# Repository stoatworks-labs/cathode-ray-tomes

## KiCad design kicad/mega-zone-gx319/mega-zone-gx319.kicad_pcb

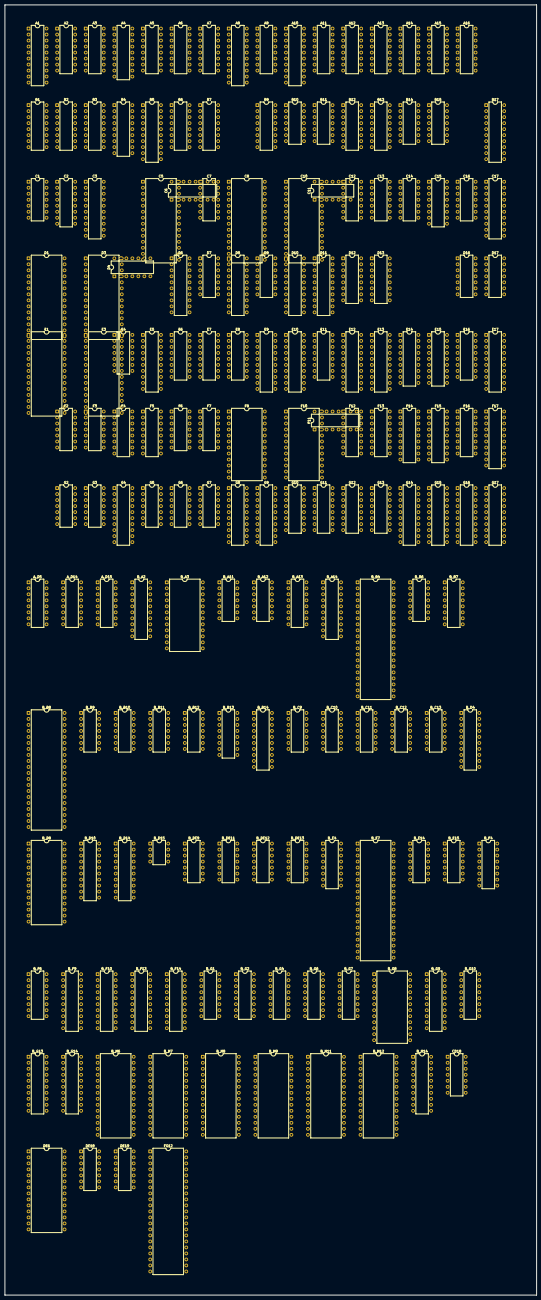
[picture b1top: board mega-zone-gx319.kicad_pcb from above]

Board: 2 copper layers, 224.9 x 545.8 mm, 171 parts (0 on the bottom side), 762 nets, no tracks yet.

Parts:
A1: 74LS244; DIP-20_W7.62mm
A2, A3: 74LS161; DIP-16_W7.62mm
A4: SRAM1K4B; DIP-18_W7.62mm
A5, A7, A9, A13, A14: 74LS157; DIP-16_W7.62mm
A6: 74LS375; DIP-16_W7.62mm
A8, A10: 74LS377; DIP-20_W7.62mm
A11: PROM256W4B; DIP-16_W7.62mm
A12, A15: 74LS174; DIP-16_W7.62mm
A16: PROM32W8B; DIP-16_W7.62mm
A_D5: 74LS157; DIP-16_W7.62mm
A_D14, A_D15: 74LS161; DIP-16_W7.62mm
B1, B6: 74LS157; DIP-16_W7.62mm
B2, B3, B12, B13: 74LS161; DIP-16_W7.62mm
B4: SRAM1K4B; DIP-18_W7.62mm
B5, B17: 74LS244; DIP-20_W7.62mm
B7: 74LS375; DIP-16_W7.62mm
B9: 74LS174; DIP-16_W7.62mm
B10, B15: 74LS86; DIP-14_W7.62mm
B11: 74LS32; DIP-14_W7.62mm
B14: 74LS04; DIP-14_W7.62mm
B_A2: 74LS373; DIP-20_W7.62mm
B_A3: 27C32; DIP-24_W15.24mm
B_A11: 74LS04; DIP-14_W7.62mm
B_A12: 74LS293; DIP-14_W7.62mm
B_A13: 74LS259; DIP-16_W7.62mm
B_A14: 74LS244; DIP-20_W7.62mm
B_B4: 8039; DIP-40_W15.24mm
B_B6: M5224P; DIP-14_W7.62mm
B_B7: 74LS138; DIP-16_W7.62mm
B_B8: AY-3-8910; DIP-40_W15.24mm
B_B9, B_B10, B_B11: 74LS293; DIP-14_W7.62mm
B_B12: 74LS32; DIP-14_W7.62mm
B_B13: 74LS139; DIP-16_W7.62mm
B_B14: 74LS240; DIP-20_W7.62mm
B_C9, B_C10, B_C12: 74LS74; DIP-14_W7.62mm
B_C11, B_C13: 74LS08; DIP-14_W7.62mm
B_D4: 74LS374; DIP-20_W7.62mm
B_D8: 501; DIP-28_W15.24mm
B_D10: 74LS244; DIP-20_W7.62mm
B_D14: 74LS240; DIP-20_W7.62mm
B_D15: 555; DIP-8_W7.62mm
B_DE9, B_DE12: 74LS32; DIP-14_W7.62mm
B_DE11: 74LS02; DIP-14_W7.62mm
B_DE13: 74LS00; DIP-14_W7.62mm
B_E4: 74LS253; DIP-16_W7.62mm
B_E7: Z80; DIP-40_W15.24mm
B_E14, B_E15: 74LS293; DIP-14_W7.62mm
B_F4: 74LS253; DIP-16_W7.62mm
B_F6: 74LS157; DIP-16_W7.62mm
B_F9, B_F10: 74LS245; DIP-20_W7.62mm
B_F13: 74LS244; DIP-20_W7.62mm
B_F14: 74LS240; DIP-20_W7.62mm
B_G1, B_G2: 74LS257; DIP-16_W7.62mm
B_G4: 74LS253; DIP-16_W7.62mm
B_G6, B_G7: 74LS157; DIP-16_W7.62mm
B_G8: SRAM2K8B; DIP-24_W15.24mm
B_G9: 74LS373; DIP-20_W7.62mm
B_G10: 74LS138; DIP-16_W7.62mm
B_G13: 74LS244; DIP-20_W7.62mm
B_G14: 74LS240; DIP-20_W7.62mm
B_H6, B_H7, B_H8, B_H9, B_H11, B_H12: 27C64; DIP-28_W15.24mm
B_H14: 74LS245; DIP-20_W7.62mm
C1: 74LS08; DIP-14_W7.62mm
C2: 74LS157; DIP-16_W7.62mm
C3: 74LS273; DIP-20_W7.62mm
C5: 083; DIP-28_W15.24mm
C6: PROM256W4B; DIP-16_W7.62mm
C7: 74LS21; DIP-14_W7.62mm
C8, C10: 27C64; DIP-28_W15.24mm
C11, C14: 74LS74; DIP-14_W7.62mm
C12, C13: 74LS86; DIP-14_W7.62mm
C15: 74LS161; DIP-16_W7.62mm
C16: 74LS107; DIP-14_W7.62mm
C17: 74LS240; DIP-20_W7.62mm
CD18: 74LS00; DIP-14_W7.62mm
D1, D3: 27C64; DIP-28_W15.24mm
D4, D9: 74LS86; DIP-14_W7.62mm
D6: 74LS377; DIP-20_W7.62mm
D7, D16: 74LS20; DIP-14_W7.62mm
D8, D10, D11: 74LS273; DIP-20_W7.62mm
D12, D13: 74LS283; DIP-16_W7.62mm
D17: 74LS32; DIP-14_W7.62mm
DE6: 27C64; DIP-28_W15.24mm
DE18: 74LS08; DIP-14_W7.62mm
DE19: 74LS10; DIP-14_W7.62mm
E1, E3: 27C64; DIP-28_W15.24mm
E4: 74LS86; DIP-14_W7.62mm
E5: 74LS273; DIP-20_W7.62mm
E6, E11: 74LS174; DIP-16_W7.62mm
E7, E8: PROM32W8B; DIP-16_W7.62mm
E9: 74LS377; DIP-20_W7.62mm
E10, E17: 74LS240; DIP-20_W7.62mm
E12: 74LS244; DIP-20_W7.62mm
E13: 74LS374; DIP-20_W7.62mm
E14, E15: SRAM1K4B; DIP-18_W7.62mm
E16: 74LS157; DIP-16_W7.62mm
F2: 74LS164; DIP-14_W7.62mm
F3: 74LS08; DIP-14_W7.62mm
F4: 74LS161; DIP-16_W7.62mm
F5: 74LS138; DIP-16_W7.62mm
F6: 74LS74; DIP-14_W7.62mm
F7: 74LS10; DIP-14_W7.62mm
F8, F10: SRAM2K8B; DIP-24_W15.24mm
F11, F16: 74LS157; DIP-16_W7.62mm
F12, F13: 74LS283; DIP-16_W7.62mm
F14, F15: SRAM1K4B; DIP-18_W7.62mm
F17: 74LS240; DIP-20_W7.62mm
FG12: KONAMI-1; DIP-42_W15.24mm
G2: 74LS164; DIP-14_W7.62mm
G3, G5: 74LS32; DIP-14_W7.62mm
G4: 74LS240; DIP-20_W7.62mm
G6, G7: 74LS74; DIP-14_W7.62mm
G8, G9, G16, G17: 74LS245; DIP-20_W7.62mm
G10, G11: 74LS157; DIP-16_W7.62mm
G12, G13: 74LS283; DIP-16_W7.62mm
G14, G15: 74LS374; DIP-20_W7.62mm

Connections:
/Color mixer/CFIX: B11.9, C11.8
/Color mixer/OCOL0: A7.4, A14.2
/Color mixer/OCOL1: A7.7, A14.5
/Color mixer/OCOL2: A7.9, A14.11
/Color mixer/OCOL3: A7.12, A14.14
/Color mixer/SEL: B1.4, B11.10
/Color mixer/TCOL''0: A13.4, A14.3
/Color mixer/TCOL''1: A13.7, A14.6
/Color mixer/TCOL''2: A13.9, A14.10
/Color mixer/TCOL''3: A13.12, A14.13
/Color mixer/~BLANK: C17.17, DE19.10, G6.9
/Color mixer/~CHBLANK: B9.7, B17.11, DE19.11
/IO/DB0: B_B8.37, B_D4.3, B_D8.20, B_E4.7, B_E7.14, B_G2.4, DE6.11
/IO/DB1: B_B8.36, B_D4.4, B_D8.21, B_E4.9, B_E7.15, B_G2.7, DE6.12
/IO/DB2: B_B8.35, B_D4.7, B_D8.22, B_E7.12, B_F4.7, B_G2.9, DE6.13
/IO/DB3: B_B8.34, B_D4.8, B_D8.23, B_E7.8, B_F4.9, B_G2.12, DE6.15
/IO/DB4: B_B8.33, B_D4.13, B_D8.24, B_E7.7, B_G1.4, B_G4.7, DE6.16
/IO/DB5: B_B8.32, B_D4.14, B_D8.25, B_E7.9, B_G1.7, B_G4.9, DE6.17
/IO/DB6: B_B8.31, B_D4.17, B_D8.26, B_E7.10, B_G1.9, DE6.18
/IO/DB7: B_B8.30, B_D4.18, B_D8.27, B_E7.13, B_G1.12, DE6.19
/IO/~AFR1: B_B13.11, B_DE13.9
/IO/~AFR2: B_B12.8, B_DE13.13
/IO/~CABINP: B_B7.12, B_E4.1, B_E4.15, B_F4.1, B_F4.15, B_G4.1, B_G4.15
/IO/~CSYNC: B17.8, C17.8, DE18.11
/IO/~DIP: B_B7.11, B_G1.15, B_G2.15
/IO/~VBLANK: B_B14.3, B_D14.2, B_E14.10, B_E15.10
/Main CPU/BLANK: B_C9.11, B_C12.3, B_D14.18
/Main CPU/CLKE: B_D10.14, FG12.15
/Main CPU/CLKQ: B_D10.16, FG12.17
/Main CPU/H1B: B_A14.5, B_C10.11, B_D8.10, B_D14.6, B_D14.15
/Main CPU/H2B: B_A14.7, B_C10.12, B_D8.9, B_D10.6, B_D14.4, B_DE9.12, B_F6.1, B_G6.1, B_G7.1
/Main CPU/INTSND: B_A14.16, B_C9.3
/Main CPU/INTST: B_A14.14, B_C12.4
/Main CPU/LACH: B_D14.13, B_D14.14, B_G9.11
/Main CPU/MA0: B_F14.13, B_G13.9, B_H6.10, B_H7.10, B_H8.10, B_H9.10, B_H11.10, B_H12.10
/Main CPU/MA1: B_A13.1, B_F14.11, B_G13.12, B_H6.9, B_H7.9, B_H8.9, B_H9.9, B_H11.9, B_H12.9
/Main CPU/MA2: B_A13.2, B_F14.8, B_G13.7, B_H6.8, B_H7.8, B_H8.8, B_H9.8, B_H11.8, B_H12.8
/Main CPU/MA3: B_A13.3, B_G13.14, B_G14.17, B_H6.7, B_H7.7, B_H8.7, B_H9.7, B_H11.7, B_H12.7
/Main CPU/MA4: B_G13.5, B_G14.2, B_H6.6, B_H7.6, B_H8.6, B_H9.6, B_H11.6, B_H12.6
/Main CPU/MA5: B_G13.16, B_G14.15, B_H6.5, B_H7.5, B_H8.5, B_H9.5, B_H11.5, B_H12.5
/Main CPU/MA6: B_G13.3, B_G14.4, B_H6.4, B_H7.4, B_H8.4, B_H9.4, B_H11.4, B_H12.4
/Main CPU/MA7: B_G13.18, B_G14.13, B_H6.3, B_H7.3, B_H8.3, B_H9.3, B_H11.3, B_H12.3
/Main CPU/MA8: B_F13.9, B_G14.6, B_H6.25, B_H7.25, B_H8.25, B_H9.25, B_H11.25, B_H12.25
/Main CPU/MA9: B_F13.12, B_G14.11, B_H6.24, B_H7.24, B_H8.24, B_H9.24, B_H11.24, B_H12.24
/Main CPU/MA10: B_F13.7, B_G14.8, B_H6.21, B_H7.21, B_H8.21, B_H9.21, B_H11.21, B_H12.21
/Main CPU/MA11: B_B13.2, B_B13.14, B_F13.14, B_H6.23, B_H7.23, B_H8.23, B_H9.23, B_H11.23, B_H12.23
/Main CPU/MA12: B_B13.3, B_B13.13, B_F13.5, B_H6.2, B_H7.2, B_H8.2, B_H9.2, B_H11.2, B_H12.2
/Main CPU/MA13: B_F13.18, B_G10.1
/Main CPU/MA14: B_DE11.6, B_F13.3, B_G10.2
/Main CPU/MA15: B_DE11.5, B_F13.16, B_G10.3
/Main CPU/MA'0: B_G6.10, F16.13, F17.18, G10.13
/Main CPU/MA'1: B_G6.6, F16.6, F17.14, G10.10
/Main CPU/MA'2: B_G6.13, F16.10, F17.7, G10.6
/Main CPU/MA'3: B_G6.3, F16.3, F17.5, G11.3
/Main CPU/MA'4: B_F6.10, E16.10, E17.16, G10.3
/Main CPU/MA'5: B_F6.6, E16.13, E17.18, G11.13
/Main CPU/MA'6: B_F6.13, E16.3, E17.3, F11.6
/Main CPU/MA'7: B_F6.3, E16.6, E17.14, F11.3
/Main CPU/MA'8: B_G7.3, DE18.9, F11.13, F17.16
/Main CPU/MA'9: B_G7.6, DE18.4, F11.10, F17.3
/Main CPU/MA'10: B_G7.13, F17.12, G11.10
/Main CPU/MA''0: B_G13.11, FG12.30
/Main CPU/MA''1: B_G13.8, FG12.31
/Main CPU/MA''2: B_G13.13, FG12.32
/Main CPU/MA''3: B_G13.6, FG12.33
/Main CPU/MA''4: B_G13.15, FG12.34
/Main CPU/MA''5: B_G13.4, FG12.35
/Main CPU/MA''6: B_G13.17, FG12.36
/Main CPU/MA''7: B_G13.2, FG12.37
/Main CPU/MA''8: B_F13.11, FG12.38
/Main CPU/MA''9: B_F13.8, FG12.39
/Main CPU/MA''10: B_F13.13, FG12.40
/Main CPU/MA''11: B_F13.6, FG12.41
/Main CPU/MA''12: B_F13.15, FG12.42
/Main CPU/MA''13: B_F13.2, FG12.1
/Main CPU/MA''14: B_F13.17, FG12.2
/Main CPU/MA''15: B_F13.4, FG12.3
/Main CPU/MBS: B_F14.2, FG12.26
/Main CPU/MD0: B_F9.11, G8.11, G9.11, G14.13, G15.13, G16.11, G17.9
/Main CPU/MD1: B_F9.12, G8.12, G9.12, G14.8, G15.8, G16.12, G17.8
/Main CPU/MD2: B_F9.13, G8.13, G9.13, G14.14, G15.14, G16.13, G17.7
/Main CPU/MD3: B_F9.14, G8.14, G9.14, G14.7, G15.7, G16.14, G17.6
/Main CPU/MD4: B_F9.15, G8.15, G9.15, G14.17, G15.17, G16.15, G17.5
/Main CPU/MD5: B_F9.16, G8.16, G9.16, G14.4, G15.4, G16.16, G17.4
/Main CPU/MD6: B_F9.17, G8.17, G9.17, G14.18, G15.18, G16.17, G17.3
/Main CPU/MD7: B_F9.18, G8.18, G9.18, G14.3, G15.3, G16.18, G17.2
/Main CPU/MD'0: B_A13.13, B_F10.9, B_G9.2, B_G9.3, B_H6.11, B_H7.11, B_H8.11, B_H9.11, B_H11.11, B_H12.11, B_H14.16
/Main CPU/MD'1: B_F10.8, B_G9.4, B_G9.5, B_H6.12, B_H7.12, B_H8.12, B_H9.12, B_H11.12, B_H12.12, B_H14.14
/Main CPU/MD'2: B_F10.7, B_G9.6, B_G9.7, B_H6.13, B_H7.13, B_H8.13, B_H9.13, B_H11.13, B_H12.13, B_H14.12
/Main CPU/MD'3: B_F10.6, B_G9.8, B_G9.9, B_H6.15, B_H7.15, B_H8.15, B_H9.15, B_H11.15, B_H12.15, B_H14.11
/Main CPU/MD'4: B_F10.5, B_G9.12, B_G9.13, B_H6.16, B_H7.16, B_H8.16, B_H9.16, B_H11.16, B_H12.16, B_H14.13
/Main CPU/MD'5: B_F10.4, B_G9.14, B_G9.15, B_H6.17, B_H7.17, B_H8.17, B_H9.17, B_H11.17, B_H12.17, B_H14.15
/Main CPU/MD'6: B_F10.3, B_G9.16, B_G9.17, B_H6.18, B_H7.18, B_H8.18, B_H9.18, B_H11.18, B_H12.18, B_H14.17
/Main CPU/MD'7: B_F10.2, B_G9.18, B_G9.19, B_H6.19, B_H7.19, B_H8.19, B_H9.19, B_H11.19, B_H12.19, B_H14.18
/Main CPU/MD''0: B_H14.4, G17.11
/Main CPU/MD''1: B_H14.6, G17.12
/Main CPU/MD''2: B_H14.8, G17.13
/Main CPU/MD''3: B_H14.9, G17.14
/Main CPU/MD''4: B_H14.7, G17.15
/Main CPU/MD''5: B_H14.5, G17.16
/Main CPU/MD''6: B_H14.3, G17.17
/Main CPU/MD''7: B_H14.2, G17.18
/Main CPU/MD'''0: B_F10.11, FG12.12
/Main CPU/MD'''1: B_F10.12, FG12.10
/Main CPU/MD'''2: B_F10.13, FG12.9
/Main CPU/MD'''3: B_F10.14, FG12.8
/Main CPU/MD'''4: B_F10.15, FG12.7
/Main CPU/MD'''5: B_F10.16, FG12.6
/Main CPU/MD'''6: B_F10.17, FG12.5
/Main CPU/MD'''7: B_F10.18, FG12.4
/Main CPU/MRD: B_B14.11, B_D10.12, B_DE12.13, B_DE13.5, B_H14.1
/Main CPU/MRD': E17.9, F17.11, G17.1
/Main CPU/MR~W: B_D10.8, B_F10.1, FG12.13
/Main CPU/MWR: D16.4, DE19.4, F17.9
/Main CPU/~CRAM': C17.14, D17.12
/Main CPU/~CRAM: B_B13.5, B_B14.4, B_C13.4
/Main CPU/~FIRQ: B_C12.9, FG12.25
/Main CPU/~INTMAIN: B_B7.10, B_C12.11
/Main CPU/~IRQ: B_C12.5, FG12.24
/Main CPU/~LACH: B_D14.7, B_DE12.12, B_DE13.4
/Main CPU/~LATCHOE: B_DE12.8, B_DE13.2, B_G9.1
/Main CPU/~MLATCH: B_A13.14, B_B13.12
/Main CPU/~MROM0: B_G10.13, B_H12.20
/Main CPU/~MROM1: B_G10.12, B_H11.20
/Main CPU/~MROM2: B_G10.11, B_H9.20
/Main CPU/~MROM3: B_G10.10, B_H8.20
/Main CPU/~MROM4: B_G10.9, B_H7.20
/Main CPU/~MROM5: B_G10.7, B_H6.20
/Main CPU/~MSHRAM: B_B13.7, B_C13.1, B_DE9.2, B_F9.19
/Main CPU/~OBJRAM: B11.12, E17.5, G16.19
/Main CPU/~RESET: B_A13.15, B_B4.4, B_B8.23, B_B14.8, B_C11.9, B_C11.12, B_C13.8, B_E7.26, FG12.19
/Main CPU/~SCROLLX: E17.12, G14.11
/Main CPU/~SCROLLY: E17.7, G15.11
/Main CPU/~VRAM': C17.16, D17.1
/Main CPU/~VRAM: B_B13.4, B_B14.2, B_C13.5
/Objects 2/COL10: A7.3, B6.2, B7.3
/Objects 2/COL11: A7.6, B6.5, B7.5
/Objects 2/COL12: A7.10, B6.11, B7.11
/Objects 2/COL13: A7.13, B6.14, B7.13
/Objects 2/COL20: A5.2, A6.3, A7.2
/Objects 2/COL21: A5.5, A6.5, A7.5
/Objects 2/COL22: A5.11, A6.11, A7.11
/Objects 2/COL23: A5.14, A6.13, A7.14
/Objects 2/COL'0: A5.3, B6.3, C6.12
/Objects 2/COL'1: A5.6, B6.6, C6.11
/Objects 2/COL'2: A5.10, B6.10, C6.10
/Objects 2/COL'3: A5.13, B6.13, C6.9
/Objects 2/OCLK1: A1.11, B2.2, B3.2, B5.19, C2.4
/Objects 2/OCLK2: A1.6, A2.2, A3.2, B5.1, C2.7
/Objects 2/OCLK3: B7.4, B7.12, C2.9
/Objects 2/OCLK4: A6.4, A6.12, C2.12
/Objects 2/OPCK: C2.2, C2.6, C2.11, C2.13, C5.1, D6.11, G4.9
/Objects 2/PXCK1: B17.4, C2.10, C2.14, C17.18
/Objects 2/PXCK2: C2.3, C2.5, E10.16
/Objects 2/XPOS10: B2.14, B4.17
/Objects 2/XPOS11: B2.13, B4.4
/Objects 2/XPOS12: B2.12, B4.5
/Objects 2/XPOS13: B2.11, B4.7
/Objects 2/XPOS14: B3.14, B4.3
/Objects 2/XPOS15: B3.13, B4.16
/Objects 2/XPOS16: B3.12, B4.15
/Objects 2/XPOS17: B3.11, B4.6
/Objects 2/XPOS20: A2.14, A4.1
/Objects 2/XPOS21: A2.13, A4.17
/Objects 2/XPOS22: A2.12, A4.16
/Objects 2/XPOS23: A2.11, A4.15
/Objects 2/XPOS24: A3.14, A4.2
/Objects 2/XPOS25: A3.13, A4.3
/Objects 2/XPOS26: A3.12, A4.4
/Objects 2/XPOS27: A3.11, A4.5
/Objects 2/~COL10: B7.2, C7.12
/Objects 2/~COL11: B7.6, C7.10
/Objects 2/~COL12: B7.10, C7.13
/Objects 2/~COL13: B7.14, C7.9
/Objects 2/~COL20: A6.2, C7.1
/Objects 2/~COL21: A6.6, C7.2
/Objects 2/~COL22: A6.10, C7.4
/Objects 2/~COL23: A6.14, C7.5
/Objects 2/~LB1EN: A5.15, B1.1, C1.12, C14.9
/Objects 2/~LB2EN: A7.1, B6.15, C1.1, C2.1, C14.8, C14.12
/Objects 2/~OBEN1: B4.8, C1.11
/Objects 2/~OBEN2: A4.8, C1.3
/Objects 2/~OBEN'': C1.2, C1.13, D6.12
/Objects 2/~ODB5L1: B1.12, B2.9, B3.9
/Objects 2/~ODB5L2: A2.9, A3.9, B1.9
/Objects 2/~OSEL1: B1.2, B6.1, C7.8
/Objects 2/~OSEL2: A5.1, B1.3, C7.6
/Objects/COL0: C5.16, C6.5
/Objects/COL1: C5.13, C6.6
/Objects/COL2: C5.17, C6.7
/Objects/COL3: C5.12, C6.4
/Objects/DMA: CD18.1, DE19.1, G7.8
/Objects/FLIPX: E5.4, E6.12
/Objects/FLIPX': D6.8, E4.10, E4.12, E5.5
/Objects/FLIPX'': C5.2, D6.9
/Objects/FLIPY: E5.7, E6.10
/Objects/FLIPY': D4.2, D4.5, D4.13, E4.5, E5.6
/Objects/H2': C17.7, D16.5, DE18.5, DE18.10, DE19.5, E13.11, E16.1, F16.1
/Objects/OA0: A_D15.14, E14.5, E15.5, F16.14
/Objects/OA1: A_D15.13, E14.6, E15.6, F16.5
/Objects/OA2: A_D15.12, E14.7, E15.7, F7.13, F16.11
/Objects/OA3: A_D15.11, E14.4, E15.4, F7.2, F16.2
/Objects/OA4: A_D14.14, E14.3, E15.3, E16.11
/Objects/OA5: A_D14.13, E14.2, E15.2, E16.14
/Objects/OA6: A_D14.12, E14.1, E15.1, E16.2
/Objects/OA7: A_D14.11, E14.17, E15.17, E16.5, F7.1
/Objects/OBA0: F14.5, F15.5, F16.12
/Objects/OBA1: F14.6, F15.6, F16.7
/Objects/OBA2: F14.7, F15.7, F16.9
/Objects/OBA3: F14.4, F15.4, F16.4
/Objects/OBA4: E16.9, F14.3, F15.3
/Objects/OBA5: E16.12, F14.2, F15.2
/Objects/OBA6: E16.4, F14.1, F15.1
/Objects/OBA7: E16.7, F14.17, F15.17
/Objects/OBA8: DE18.8, F14.16, F15.16
/Objects/OBA9: DE18.6, F14.15, F15.15
/Objects/OBD0: E13.4, F15.14, G16.5
/Objects/OBD1: E13.17, F15.13, G16.4
/Objects/OBD2: E13.7, F15.12, G16.3
/Objects/OBD3: E13.13, F15.11, G16.2
/Objects/OBD4: E13.18, F14.14, G16.9
/Objects/OBD5: E13.3, F14.13, G16.8
/Objects/OBD6: E13.14, F14.12, G16.7
/Objects/OBD7: E13.8, F14.11, G16.6
/Objects/OCA0: D4.4, E5.15
/Objects/OCA1: D4.12, E5.19
/Objects/OCA2: D4.1, E5.2
/Objects/OCA3: E4.4, E5.16
/Objects/OCD0: C5.6, E1.11, E3.11
/Objects/OCD1: C5.10, E1.12, E3.12
/Objects/OCD2: C5.23, E1.13, E3.13
/Objects/OCD3: C5.19, E1.15, E3.15
/Objects/OCD4: C5.5, E1.16, E3.16
/Objects/OCD5: C5.9, E1.17, E3.17
/Objects/OCD6: C5.24, E1.18, E3.18
/Objects/OCD7: C5.20, E1.19, E3.19
/Objects/OCD8: C5.4, D1.11, D3.11
/Objects/OCD9: C5.8, D1.12, D3.12
/Objects/OCD10: C5.25, D1.13, D3.13
/Objects/OCD11: C5.21, D1.15, D3.15
/Objects/OCD12: C5.3, D1.16, D3.16
/Objects/OCD13: C5.7, D1.17, D3.17
/Objects/OCD14: C5.26, D1.18, D3.18
/Objects/OCD15: C5.22, D1.19, D3.19
/Objects/OCHA0: D1.10, D3.10, D4.6, E1.10, E3.10
/Objects/OCHA1: D1.9, D3.9, D4.11, E1.9, E3.9
/Objects/OCHA2: D1.8, D3.8, D4.3, E1.8, E3.8
/Objects/OCHA3: D1.7, D3.7, E1.7, E3.7, E4.11
/Objects/OCHA4: D1.6, D3.6, E1.6, E3.6, E4.8
/Objects/OCHA5: D1.5, D3.5, E1.5, E3.5, E4.6
/Objects/OCHA6: C3.9, D1.4, D3.4, E1.4, E3.4
/Objects/OCHA7: C3.6, D1.3, D3.3, E1.3, E3.3
/Objects/OCHA8: C3.5, D1.25, D3.25, E1.25, E3.25
/Objects/OCHA9: C3.2, D1.24, D3.24, E1.24, E3.24
/Objects/OCHA10: C3.15, D1.21, D3.21, E1.21, E3.21
/Objects/OCHA11: C3.16, D1.23, D3.23, E1.23, E3.23
/Objects/OCHA12: C3.19, D1.2, D3.2, E1.2, E3.2
/Objects/OD0: E12.4, E13.5, E14.14
/Objects/OD1: E12.15, E13.16, E14.13
/Objects/OD2: E12.6, E13.6, E14.12
/Objects/OD3: E12.8, E13.12, E14.11
/Objects/OD4: E12.17, E13.19, E15.14
/Objects/OD5: E12.2, E13.2, E15.13
/Objects/OD6: E12.13, E13.15, E15.12
/Objects/OD7: E12.11, E13.9, E15.11
/Objects/OD'0: A2.3, B2.3, C3.8, D11.14, E6.4, E12.16
/Objects/OD'1: A2.4, B2.4, C3.7, D11.18, E6.3, E12.5
/Objects/OD'2: A2.5, B2.5, C3.4, D11.3, E6.6, E12.14
/Objects/OD'3: A2.6, B2.6, C3.3, D11.4, E6.14, E12.12
/Objects/OD'4: A3.3, B3.3, C3.14, D11.7, E12.3
/Objects/OD'5: A3.4, B3.4, C3.17, D11.13, E12.18
/Objects/OD'6: A3.5, B3.5, C3.18, D11.8, E6.13, E12.7
/Objects/OD'7: A3.6, B3.6, C3.13, D11.17, E6.11, E12.9
/Objects/OP0OP1: C5.27, F3.3
/Objects/PAL0: D6.3, E6.5
/Objects/PAL1: D6.4, E6.2
/Objects/PAL2: D6.7, E6.7
/Objects/PAL3: D6.18, E6.15
/Objects/PAL'0: C6.3, D6.2
/Objects/PAL'1: C6.2, D6.5
/Objects/PAL'2: C6.1, D6.6
/Objects/PAL'3: C6.15, D6.19
/Objects/V1: B12.7, B12.10, C12.1, C14.5, D12.5
/Objects/V2: B12.14, C12.4, D12.3
/Objects/V4: B12.13, C12.9, D12.14
/Objects/V8: B12.12, C12.12, D12.12
/Objects/V16: B12.11, C13.1, D13.5, G6.11
/Objects/V32: B13.14, C13.4, D13.3, F7.5
/Objects/V64: B13.13, C13.9, D13.14, F7.4
/Objects/V128: B13.12, C13.12, D13.12, F7.3
/Objects/WRIH: D16.2, DE19.2, DE19.3, E10.5
/Objects/YPOS0: D11.15, D12.6
/Objects/YPOS1: D11.19, D12.2
/Objects/YPOS2: D11.2, D12.15
/Objects/YPOS3: D11.5, D12.11
/Objects/YPOS4: D11.6, D13.6
/Objects/YPOS5: D11.12, D13.2
/Objects/YPOS6: D11.9, D13.15
/Objects/YPOS7: D11.16, D13.11
/Objects/~DMWR: DE19.12, E14.10, E15.10
/Objects/~OACNTEN': F6.9, G5.10
/Objects/~OBEN': D6.13, G5.8
/Objects/~OBEN: E5.12, G5.9
/Objects/~OCHAH: D1.20, D4.8, E1.20
/Objects/~OCHAL: C3.12, D3.20, D4.9, E3.20
/Objects/~ODB0: D7.1, E6.9, F5.15
/Objects/~ODB1: D7.5, D11.11, F5.14
/Objects/~ODB3: C3.11, D7.2, E5.11, F5.12
/Objects/~ODB5: B1.11, B1.13, D6.1, F5.10, F6.11
/Objects/~OP2: E4.13, G4.5
/SA0: B_A11.9, B_B12.4, B_D10.18, B_DE11.11, B_E4.14, B_F4.14, B_G1.1, B_G2.1, B_G4.14, B_G6.11, DE6.10
/SA1: B_D10.9, B_DE11.2, B_E4.2, B_F4.2, B_G4.2, B_G6.5, DE6.9
/SA2: B_E7.32, B_G6.14, DE6.8
/SA3: B_E7.33, B_G6.2, DE6.7
/SA4: B_E7.34, B_F6.11, DE6.6
/SA5: B_E7.35, B_F6.5, DE6.5
/SA6: B_E7.36, B_F6.14, DE6.4
/SA7: B_E7.37, B_F6.2, DE6.3
/SA8: B_E7.38, B_G7.2, DE6.25
/SA9: B_E7.39, B_G7.5, DE6.24
/SA10: B_E7.40, B_G7.14, DE6.21
/Shared RAM/VA0: B_G6.9, B_G8.8
/Shared RAM/VA1: B_G6.7, B_G8.7
/Shared RAM/VA2: B_G6.12, B_G8.6
/Shared RAM/VA3: B_G6.4, B_G8.5
/Shared RAM/VA4: B_F6.9, B_G8.4
/Shared RAM/VA5: B_F6.7, B_G8.3
/Shared RAM/VA6: B_F6.12, B_G8.2
/Shared RAM/VA7: B_F6.4, B_G8.1
/Shared RAM/VA8: B_G7.4, B_G8.23
/Shared RAM/VA9: B_G7.7, B_G8.22
/Shared RAM/VA10: B_G7.12, B_G8.19
/Shared RAM/VD0: B_D8.1, B_F9.9, B_G8.9
/Shared RAM/VD1: B_D8.2, B_F9.8, B_G8.10
/Shared RAM/VD2: B_D8.3, B_F9.7, B_G8.11
/Shared RAM/VD3: B_D8.4, B_F9.6, B_G8.13
/Shared RAM/VD4: B_D8.5, B_F9.5, B_G8.14
/Shared RAM/VD5: B_D8.6, B_F9.4, B_G8.15
/Shared RAM/VD6: B_D8.7, B_F9.3, B_G8.16
/Shared RAM/VD7: B_D8.8, B_F9.2, B_G8.17
/Shared RAM/~MWRAMW: B_DE9.3, B_F9.1, B_G7.10
/Shared RAM/~SRD: B_D8.13, B_E7.21
/Shared RAM/~SSHRAM: B_B7.7, B_D8.12
/Shared RAM/~SVRAMW: B_DE9.6, B_G7.11
/Shared RAM/~WAIT: B_D8.19, B_E7.24
/Shared RAM/~WRIT: B_DE9.1, B_DE12.11
/Sub CPU/CK1M79: B_A11.12, B_B8.22
/Sub CPU/CK7M16: B_A12.9, B_A12.11, B_D14.8
/Sub CPU/IA0: B_A2.12, B_A3.8
/Sub CPU/IA1: B_A2.9, B_A3.7
/Sub CPU/IA2: B_A2.15, B_A3.6
/Sub CPU/IA3: B_A2.6, B_A3.5
/Sub CPU/IA4: B_A2.16, B_A3.4
/Sub CPU/IA5: B_A2.5, B_A3.3
/Sub CPU/IA6: B_A2.19, B_A3.2
/Sub CPU/IA7: B_A2.2, B_A3.1
/Sub CPU/IA8: B_A3.23, B_B4.21
/Sub CPU/IA9: B_A3.22, B_B4.22
/Sub CPU/IA10: B_A3.19, B_B4.23
/Sub CPU/IA11: B_A3.21, B_B4.24
/Sub CPU/ID0: B_A2.13, B_A3.9, B_B4.12, B_D4.2
/Sub CPU/ID1: B_A2.8, B_A3.10, B_B4.13, B_D4.5
/Sub CPU/ID2: B_A2.14, B_A3.11, B_B4.14, B_D4.6
/Sub CPU/ID3: B_A2.7, B_A3.13, B_B4.15, B_D4.9
/Sub CPU/ID4: B_A2.17, B_A3.14, B_B4.16, B_D4.12
/Sub CPU/ID5: B_A2.4, B_A3.15, B_B4.17, B_D4.15
/Sub CPU/ID6: B_A2.18, B_A3.16, B_B4.18, B_D4.16
/Sub CPU/ID7: B_A2.3, B_A3.17, B_B4.19, B_D4.19
/Sub CPU/SA11: B_E7.1, DE6.23
/Sub CPU/SA12: B_E7.2, DE6.2
/Sub CPU/SA13: B_B7.1, B_E7.3
/Sub CPU/SA14: B_B7.2, B_E7.4
/Sub CPU/SA15: B_B7.3, B_E7.5
/Sub CPU/YA0: B_B4.35, B_B8.21
/Sub CPU/YA1: B_B4.36, B_B8.20
/Sub CPU/YA2: B_B4.37, B_B8.19
/Sub CPU/YA4: B_B8.17, B_B9.9, B_B9.11
/Sub CPU/YA5: B_B8.16, B_B9.5
/Sub CPU/YA6: B_B8.15, B_B9.4
/Sub CPU/YA7: B_B8.14, B_B9.8
/Sub CPU/~AYBC1: B_B8.29, B_DE11.1
/Sub CPU/~AYDIR: B_B8.27, B_DE11.13
/Sub CPU/~CODE: B_B7.13, B_D4.11
/Sub CPU/~IINT: B_B4.6, B_C10.6
/Sub CPU/~IRD: B_B4.8, B_D4.1
/Sub CPU/~SINT: B_C9.8, B_E7.16
/Sub CPU/~SIORQ: B_DE9.10, B_DE12.2, B_E7.20
/Sub CPU/~SM1: B_A11.11, B_DE9.9, B_E7.27
/Sub CPU/~SMREQ: B_B7.4, B_B7.5, B_E7.19
/Sub CPU/~SNMI: B_C9.5, B_E7.17
/Sub CPU/~SRFSH: B_B7.6, B_E7.28
/Sub CPU/~SROM: B_B7.15, DE6.20
/Sub CPU/~START: B_B7.14, B_C10.3
/Sub CPU/~WDOG: B_B7.9, B_B12.5, B_B12.10
/Tiles/CD0: B9.4, F10.9, G9.9
/Tiles/CD1: B9.3, F10.10, G9.8
/Tiles/CD2: B9.13, F10.11, G9.7
/Tiles/CD3: B9.11, F10.13, G9.6
/Tiles/CD4: F10.14, G9.5
/Tiles/CD5: D10.14, F10.15, G9.4
/Tiles/CD6: D10.7, F10.16, G9.3
/Tiles/CD7: D10.18, F10.17, G9.2
/Tiles/FIX: B14.4, F12.7, G11.11, G12.7, G14.1, G15.1
/Tiles/HF2: B15.8, G12.5
/Tiles/HF4: B15.11, G12.3
/Tiles/HF8: B15.3, G12.14
/Tiles/HF16: E7.14, E8.14, E9.19, G12.12
/Tiles/HF32: E7.13, E8.13, E9.2, E10.2, G13.5
/Tiles/HF64: E9.6, G13.3
/Tiles/HF128: E9.9, G13.14
/Tiles/HS2: E11.11, G12.4
/Tiles/HS2'': B10.9, D10.12
/Tiles/HS4: E11.13, G12.1
/Tiles/HS4'': D9.9, D10.9
/Tiles/HS8: G10.14, G12.13
/Tiles/HS16: G10.11, G12.10
/Tiles/HS32: G10.5, G13.4
/Tiles/HS64: G11.2, G13.1
/Tiles/HS128: G10.2, G13.13
/Tiles/HS'2: D10.13, E11.10
/Tiles/HS'4: D10.8, E11.12
/Tiles/PXCK2': A8.11, A10.11, A12.9, A15.9, E10.3
/Tiles/SCRX0: F12.6, G14.12
/Tiles/SCRX1: F12.2, G14.9
/Tiles/SCRX2: F12.15, G14.15
/Tiles/SCRX3: F12.11, G14.6
/Tiles/SCRX4: F13.6, G14.16
/Tiles/SCRX5: F13.2, G14.5
/Tiles/SCRX6: F13.15, G14.19
/Tiles/SCRX7: F13.11, G14.2
/Tiles/SCRY0: E11.14, G15.12
/Tiles/SCRY0F: A10.12, A13.1
/Tiles/SCRY1: G12.6, G15.9
/Tiles/SCRY2: G12.2, G15.15
/Tiles/SCRY3: G12.15, G15.6
/Tiles/SCRY4: G12.11, G15.16
/Tiles/SCRY5: G13.6, G15.5
/Tiles/SCRY6: G13.2, G15.19
/Tiles/SCRY7: G13.15, G15.2
/Tiles/SCRY'0: C11.2, CD18.12, E11.15
/Tiles/SCRY''0: B9.15, B10.12
/Tiles/TA0: F8.8, F10.8, G10.12
/Tiles/TA1: F8.7, F10.7, G10.9
/Tiles/TA2: F8.6, F10.6, G10.7
/Tiles/TA3: F8.5, F10.5, G11.4
/Tiles/TA4: F8.4, F10.4, G10.4
/Tiles/TA5: F8.3, F10.3, G11.12
/Tiles/TA6: F8.2, F10.2, F11.7
/Tiles/TA7: F8.1, F10.1, F11.4
/Tiles/TA8: F8.23, F10.23, F11.12
/Tiles/TA9: F8.22, F10.22, F11.9
/Tiles/TA10: F8.19, F10.19, G11.9
/Tiles/TCHA0: B10.8, C8.10, C10.10
/Tiles/TCHA1: C8.9, C10.9, D9.8
/Tiles/TCHA2: C8.8, C10.8, D9.3
/Tiles/TCHA3: C8.7, C10.7, D9.11
/Tiles/TCHA4: C8.6, C10.6, D9.6
/Tiles/TCHA5: C8.5, C10.5, D8.2
/Tiles/TCHA6: C8.4, C10.4, D8.5
/Tiles/TCHA7: C8.3, C10.3, D8.6
/Tiles/TCHA8: C8.25, C10.25, D8.19
/Tiles/TCHA9: C8.24, C10.24, D8.16
/Tiles/TCHA10: C8.21, C10.21, D8.12
/Tiles/TCHA11: C8.23, C10.23, D8.15
/Tiles/TCHA12: C8.2, C10.2, D8.9
/Tiles/TCHD0: A8.18, C8.11, C10.11
/Tiles/TCHD1: A8.17, C8.12, C10.12
/Tiles/TCHD2: A8.7, C8.13, C10.13
/Tiles/TCHD3: A8.3, C8.15, C10.15
/Tiles/TCHD4: A8.13, C8.16, C10.16
/Tiles/TCHD5: A8.14, C8.17, C10.17
/Tiles/TCHD6: A8.8, C8.18, C10.18
/Tiles/TCHD7: A8.4, C8.19, C10.19
/Tiles/TCHD'0: A8.19, A9.2
/Tiles/TCHD'1: A8.16, A9.5
/Tiles/TCHD'2: A8.6, A9.11
/Tiles/TCHD'3: A8.2, A9.14
/Tiles/TCHD'4: A8.12, A9.3
/Tiles/TCHD'5: A8.15, A9.6
/Tiles/TCHD'6: A8.9, A9.10
/Tiles/TCHD'7: A8.5, A9.13
/Tiles/TCODE0: A9.4, A11.5
/Tiles/TCODE1: A9.7, A11.6
/Tiles/TCODE2: A9.9, A11.7
/Tiles/TCODE3: A9.12, A11.4
/Tiles/TCOL0: A11.12, A12.4, A13.3
/Tiles/TCOL1: A11.11, A12.6, A13.6
/Tiles/TCOL2: A11.10, A12.11, A13.10
/Tiles/TCOL3: A11.9, A12.13, A13.13
/Tiles/TCOL'0: A12.5, A13.2
/Tiles/TCOL'1: A12.7, A13.5
/Tiles/TCOL'2: A12.10, A13.11
/Tiles/TCOL'3: A12.12, A13.14
/Tiles/THFLIP: B10.1, B10.10, D9.10, D10.6
/Tiles/TPAL0: A10.17, B9.5
/Tiles/TPAL1: A10.18, B9.2
/Tiles/TPAL2: A10.3, B9.12
/Tiles/TPAL3: A10.14, B9.10
/Tiles/TPAL'0: A10.16, A11.3
/Tiles/TPAL'1: A10.19, A11.2
/Tiles/TPAL'2: A10.2, A11.1
/Tiles/TPAL'3: A10.15, A11.15
/Tiles/TVFLIP: D9.2, D9.5, D9.13, D10.15
/Tiles/V1S': D9.1, D10.2
/Tiles/V2S': D9.12, D10.5
/Tiles/V4S': D9.4, D10.16
/Tiles/VD0: D8.3, F8.9, G8.9
/Tiles/VD1: D8.4, F8.10, G8.8
/Tiles/VD2: D8.7, F8.11, G8.7
/Tiles/VD3: D8.18, F8.13, G8.6
/Tiles/VD4: D8.17, F8.14, G8.5
/Tiles/VD5: D8.14, F8.15, G8.4
/Tiles/VD6: D8.13, F8.16, G8.3
/Tiles/VD7: D8.8, F8.17, G8.2
/Tiles/VF1: C12.3, F12.5
/Tiles/VF2: C12.6, F12.3
/Tiles/VF4: C12.8, F12.14
/Tiles/VF8: C12.11, F12.12
/Tiles/VF16: C13.3, F13.5
/Tiles/VF32: C13.6, F13.3
/Tiles/VF64: C13.8, F13.14
/Tiles/VF128: C13.11, F13.12
/Tiles/VS1: D10.3, F12.4
/Tiles/VS2: D10.4, F12.1
/Tiles/VS4: D10.17, F12.13
/Tiles/VS8: F12.10, G11.14
/Tiles/VS16: F11.5, F13.4
/Tiles/VS32: F11.2, F13.1
/Tiles/VS64: F11.14, F13.13
/Tiles/VS128: F11.11, F13.10
/Tiles/~CRAMBE: D17.10, D17.11, G9.19
/Tiles/~CRAMWR: D17.8, F10.21, G9.1
/Tiles/~FIX': C11.12, E11.5
/Tiles/~H1: D16.1, E10.6, E10.9, F11.1, G10.1, G11.1
/Tiles/~HT1: B9.9, B10.5, B11.4, D8.11, D10.11, E10.7
/Tiles/~TCHH: B14.6, C10.22
/Tiles/~TCHL: B14.5, C8.22, D10.19
/Tiles/~VRAMBE: D17.3, D17.4, G8.19
/Tiles/~VRAMWR: D17.6, F8.21, G8.1
/Timing/16H: B14.9, C15.15
/Timing/FLIP: B10.2, B10.13, B14.13, B15.2, B15.5, B15.10, B15.13, B17.5, CD18.13, D16.9, D16.10, D16.12, D16.13, E7.15
/Timing/FLIP': B15.6, C12.2, C12.5, C12.10, C12.13, C13.2, C13.5, C13.10, C13.13, F3.12, G4.4
/Timing/H1: B17.2, C11.3, C15.14, D17.2, D17.13, E10.11, E10.13, E11.9, G7.11
/Timing/H2: B15.9, B17.17, C15.13, C17.11, F3.13
/Timing/H4: B15.12, C11.11, C15.12, F3.10, G5.5
/Timing/H8: B15.1, C15.11
/Timing/HRD0: E7.1, E8.1, E9.18
/Timing/HRD1: E7.2, E8.2, E9.3
/Timing/HRD2: E7.3, E8.3, E9.4
/Timing/HRD3: E7.4, E8.4, E9.17
/Timing/HRD4: E7.5, E8.5, E9.14
/Timing/HRD5: E7.6, E8.6, E9.7
/Timing/HRD6: E7.7, E8.7, E9.8
/Timing/HRD7: E7.9, E8.9, E9.13
/Timing/HRD'2: E7.12, E8.12, E9.5
/Timing/HRD'3: E7.11, E8.11, E9.16
/Timing/HSYNC: B12.2, B13.2, C14.3, E10.12
/Timing/OACK: A_D5.3, G4.7
/Timing/OACNTEN: A_D5.13, F6.5
/Timing/OP0: F3.2, F4.14, F5.6
/Timing/OP1: F3.1, F4.13, F5.1
/Timing/OP2: F4.12, F5.2, G4.15
/Timing/OP3: E4.9, F4.11, F5.3
/Timing/PXCK2'': C15.2, C16.1, C16.6, E9.11
/Timing/V256: B13.11, DE18.12
/Timing/~16H: B14.8, E9.1
/Timing/~FIX: B14.3, E7.10, E8.10, E9.15, E11.4
/Timing/~FLIP: F3.9, G4.16
/Timing/~H2: A_D5.2, B14.11, B17.6, C17.9, C17.13
/Timing/~HBLANK: B11.2, E9.12, E11.6
/Timing/~HSYNC60: F2.13, G2.1, G2.2
/Timing/~HSYNC68: G2.10, G5.1
/Timing/~HSYNC: B11.3, DE18.13, E10.8, F2.1, F2.2
/Timing/~LBRST: A2.1, A3.1, A_D5.10, B2.1, B3.1, C14.11, F4.1, F6.4, F6.13, G5.6
/Timing/~OACNTEN: F6.6, F6.12
/Timing/~OAOF: G4.14, G7.4
/Timing/~ODB6: D7.4, F5.9
/Timing/~OPCK: F4.2, G5.11
/Timing/~PXCK2: C16.5, E10.4, E10.17
GND: A1.1, A1.10, A1.19, A4.6, A4.7, A4.9, A6.8, A7.15, A9.15, A11.8, A11.13, A11.14, A12.8, A13.15, A15.8, A16.8, A16.15, A_D5.15, B1.15, B4.1, B4.2, B4.9, B5.10, B7.8, B9.8, B10.7, B11.5, B11.7, B12.3, B12.4, B13.6, B14.7, B15.4, B15.7, B17.1, B17.10, B17.19, B_A2.1, B_A2.10, B_A3.12, B_A3.18, B_A11.7, B_A12.7, B_A12.12, B_A12.13, B_A13.8, B_A14.1, B_A14.10, B_A14.19, B_B4.1, B_B4.20, B_B6.11, B_B7.8, B_B8.1, B_B8.24, B_B9.7, B_B9.12, B_B9.13, B_B10.7, B_B10.12, B_B10.13, B_B11.7, B_B11.12, B_B11.13, B_B12.7, B_B13.8, B_B14.1, B_B14.10, B_B14.19, B_C9.7, B_C10.7, B_C11.7, B_C12.2, B_C12.7, B_C12.12, B_C13.7, B_D8.14, B_D8.15, B_D10.1, B_D10.10, B_D10.19, B_D14.1, B_D14.10, B_D14.19, B_D15.1, B_DE9.7, B_DE11.7, B_DE12.7, B_DE13.7, B_E4.8, B_E7.29, B_E14.7, B_E15.7, B_F4.8, B_F6.15, B_F10.19, B_F13.1, B_F13.10, B_F13.19, B_F14.1, B_F14.6, B_F14.10, B_F14.15, B_F14.19, B_G1.8, B_G2.8, B_G4.8, B_G6.15, B_G7.15, B_G8.12, B_G8.18, B_G8.20, B_G9.10, B_G10.4, B_G10.5, B_G10.8, B_G13.1, B_G13.10, B_G13.19, B_G14.1, B_G14.10, B_G14.19, B_H6.14, B_H6.22, B_H7.14, B_H7.22, B_H8.14, B_H8.22, B_H9.14, B_H9.22, B_H11.14, B_H11.22, B_H12.14, B_H12.22, C1.7, C2.15, C3.10, C5.14, C6.8, C6.13, C6.14, C7.7, C8.14, C8.20, C10.14, C10.20, C11.7, C12.7, C13.7, C14.7, C16.7, C17.1, C17.10, C17.19, CD18.7, D1.14, D1.22, D3.14, D3.22, D4.7, D7.7, D8.10, D9.7, D10.10, D11.10, D12.7, D16.7, D17.7, DE6.14, DE6.22, DE18.7, DE19.7, E1.14, E1.22, E3.14, E3.22, E4.7, E5.10, E6.8, E7.8, E8.8, E10.1, E10.10, E10.19, E11.8, E12.1, E12.10, E12.19, E14.8, E14.9, E14.15, E14.16, E15.8, E15.9, E15.15, E15.16, E16.15, E17.1, E17.10, E17.19, F2.7, F3.7, F5.4, F5.5, F5.8, F6.2, F6.7, F7.7, F8.12, F8.18, F8.20, F10.12, F10.18, F10.20, F11.15, F14.8, F14.9, F15.8, F15.9, F16.15, F17.1, F17.10, F17.19, FG12.20, FG12.22, G2.7, G3.7, G4.1, G4.10, G4.19, G5.7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
unnamed: A2.15, A3.7, A3.10
unnamed: A4.14, A6.15, B5.12
unnamed: A4.13, A6.9, B5.14
unnamed: A4.12, A6.7, B5.16
unnamed: A4.11, A6.1, B5.18
unnamed: A1.14, A4.10
unnamed: A5.4, B5.2
unnamed: A5.7, B5.4
unnamed: A5.9, B5.6
unnamed: A5.12, B5.8
unnamed: A9.1, B10.6
unnamed: A10.7, B10.3
unnamed: A10.13, B10.11
unnamed: A10.6, B10.4
unnamed: A8.1, A10.1, B11.6
unnamed: A14.1, A15.14, B11.8
unnamed: A14.4, A15.11
unnamed: A14.7, A15.6
unnamed: A14.9, A15.13
unnamed: A14.12, A15.4
unnamed: A14.15, DE19.8
unnamed: A15.5, A16.13
unnamed: A15.7, A16.11
unnamed: A15.10, A16.10
unnamed: A15.12, A16.12
unnamed: A15.15, A16.14
unnamed: A_D5.11, F7.8
unnamed: A_D5.1, G7.5, G7.12
unnamed: A_D14.7, A_D14.10, A_D15.15
unnamed: A_D5.4, A_D14.2, A_D15.2
unnamed: A_D14.15, G4.6
unnamed: A_D5.9, A_D14.1, A_D15.1
unnamed: A_D5.12, A_D15.7, A_D15.10
unnamed: B2.15, B3.7, B3.10
unnamed: B4.14, B5.3, B7.1
unnamed: B4.13, B5.5, B7.7
unnamed: B4.12, B5.7, B7.9
unnamed: B4.11, B5.9, B7.15
unnamed: A1.9, B4.10
unnamed: B5.11, B6.12
unnamed: B5.13, B6.9
unnamed: B5.15, B6.7
unnamed: B5.17, B6.4
unnamed: B9.6, E11.2
unnamed: B9.14, CD18.8
unnamed: B11.1, E10.18
unnamed: B11.13, DE19.6
unnamed: B12.15, B13.7, B13.10
unnamed: B12.9, B13.9, B14.2
unnamed: B13.15, B14.1
unnamed: B14.10, CD18.2, DE19.13
unnamed: C16.9, C16.12, G6.3
unnamed: B17.3, B_A14.13
unnamed: B17.9, DE19.9
unnamed: B17.13, B17.14
unnamed: B17.15, B_A14.12
unnamed: B17.16, B_A14.11
unnamed: B17.18, B_A14.15
unnamed: B_A2.11, B_B4.11
unnamed: B_A3.20, B_B4.9
unnamed: B_A11.4, B_A11.5
unnamed: B_A11.8, B_B12.9
unnamed: B_A11.10, B_DE12.1
unnamed: B_A11.6, B_A12.10
unnamed: B_A11.13, B_A12.4
unnamed: B_A12.8, B_B11.10
unnamed: B_A13.4, B_A14.17
unnamed: B_A13.5, B_A14.2
unnamed: B_A13.7, B_A14.4
unnamed: B_A13.10, B_A14.8
unnamed: B_A13.12, B_A14.6
unnamed: B_B4.5, B_B4.7
unnamed: B_B4.38, B_C10.1
unnamed: B_B4.2, B_D14.11, B_D14.12
unnamed: B_B4.3, B_D14.9
unnamed: B_B6.1, B_B6.2
unnamed: B_B10.10, B_B11.8
unnamed: B_B10.9, B_B10.11
unnamed: B_B9.10, B_B10.8
unnamed: B_B11.9, B_B11.11
unnamed: B_B12.6, B_C11.10
unnamed: B_B12.2, B_B12.13, B_D14.16
unnamed: B_B12.3, B_B13.1
unnamed: B_B13.6, B_B14.15
unnamed: B_B12.11, B_B13.15
unnamed: B_B13.10, B_B14.6
unnamed: B_B13.9, B_B14.13
unnamed: B_B14.5, E17.15
unnamed: B_B14.7, E17.8
unnamed: B_B14.9, E17.11
unnamed: B_B14.12, C17.15
unnamed: B_B14.14, E17.13
unnamed: B_B14.16, C17.6
unnamed: B_B14.17, C17.3
unnamed: B_B14.18, C17.4
unnamed: B_C9.4, B_C11.8
unnamed: B_C9.13, B_C11.11
unnamed: B_C10.8, B_D10.4, B_DE9.13
unnamed: B_C11.13, B_DE9.8
unnamed: B_C12.10, B_F14.18
unnamed: B_C13.2, B_DE11.4
unnamed: B_C13.3, B_DE13.1
unnamed: B_C13.6, B_DE12.10
unnamed: B_C13.9, B_DE11.10
unnamed: B_C13.10, B_C13.11
unnamed: B_C13.12, B_D14.3
unnamed: B_A14.9, B_D8.11
unnamed: B_D8.18, B_DE9.5
unnamed: B_D8.17, B_DE9.4
unnamed: B_D15.6, B_D15.7
unnamed: B_D14.17, B_D15.3
unnamed: B_C13.13, B_D15.2
unnamed: B_DE11.3, B_DE11.12, B_DE12.3
unnamed: B_DE12.9, B_DE13.6
unnamed: B_D10.2, B_E7.30
unnamed: B_D10.11, B_E7.31
unnamed: B_D14.5, B_E7.6
unnamed: B_E14.9, B_E14.11
unnamed: B_DE11.8, B_E14.8
unnamed: B_DE13.11, B_E14.12, B_E14.13
unnamed: B_E15.9, B_E15.11
unnamed: B_DE11.9, B_E15.8
unnamed: B_DE13.8, B_E15.12, B_E15.13
unnamed: B_F14.7, F17.2
unnamed: B_F14.9, F17.6
unnamed: B_F14.12, F17.13
unnamed: B_G7.9, B_G8.21
unnamed: B_DE9.11, B_G10.6
unnamed: B_B12.12, B_G10.15
unnamed: B_B12.1, B_G10.14
unnamed: B_G14.18, E17.4
unnamed: B_G14.9, F17.17
unnamed: B_G14.16, E17.17
unnamed: B_G14.7, E17.6
unnamed: B_G14.14, F17.4
unnamed: B_G14.5, E17.2
unnamed: B_G14.12, F17.8
unnamed: B_G14.3, F17.15
unnamed: B_DE13.3, B_H14.19
unnamed: B_DE13.10, B_DE13.12
unnamed: C11.5, CD18.4
unnamed: C14.2, C14.6
unnamed: C16.3, C16.8
unnamed: C16.2, C17.2
unnamed: G4.12, G4.13
unnamed: CD18.5, D16.8
unnamed: CD18.6, CD18.9
unnamed: CD18.10, CD18.11
unnamed: D7.6, G4.8
unnamed: D12.4, E5.14
unnamed: D12.1, E5.18
unnamed: D12.13, E5.3
unnamed: D12.10, E5.17
unnamed: D12.9, D13.7
unnamed: D7.10, D13.4
unnamed: D7.13, D13.1
unnamed: D7.12, D13.13
unnamed: D7.9, D13.10
unnamed: D16.6, D17.5, D17.9
unnamed: D7.8, E5.13
unnamed: B14.12, E8.15
unnamed: E10.14, E10.15
unnamed: E11.3, E11.7
unnamed: CD18.3, E13.1
unnamed: F2.8, G2.8, G3.8
unnamed: F3.8, G3.10
unnamed: F3.11, G3.9
unnamed: F6.3, F7.12
unnamed: F12.9, F13.7
unnamed: B11.11, F14.10, F15.10, G16.1
unnamed: G2.11, G4.2
unnamed: G4.18, G5.2
unnamed: G5.3, G5.4
unnamed: G5.13, G6.2, G6.6
unnamed: G4.11, G6.5
unnamed: F7.6, G6.12
unnamed: G6.8, G7.3
unnamed: F7.10, G7.6
unnamed: F7.9, G7.9
unnamed: G12.9, G13.7
unnamed: B17.7, G17.19
VCC: A1.20, A2.7, A2.10, A4.18, A6.16, A11.16, A12.1, A12.16, A15.1, A15.16, A16.16, A_D5.14, A_D14.9, A_D15.9, B1.10, B1.14, B2.7, B2.10, B4.18, B5.20, B7.16, B9.1, B9.16, B10.14, B11.14, B12.1, B12.5, B12.6, B13.1, B13.3, B13.4, B13.5, B14.14, B15.14, B17.20, B_A2.20, B_A3.24, B_A11.14, B_A12.14, B_A13.16, B_A14.20, B_B4.26, B_B4.40, B_B7.16, B_B8.25, B_B8.28, B_B8.40, B_B9.14, B_B10.14, B_B11.14, B_B12.14, B_B13.16, B_B14.20, B_C9.1, B_C9.2, B_C9.10, B_C9.12, B_C9.14, B_C10.2, B_C10.4, B_C10.10, B_C10.13, B_C10.14, B_C11.14, B_C12.1, B_C12.13, B_C12.14, B_C13.14, B_D8.28, B_D10.20, B_D14.20, B_D15.4, B_D15.8, B_DE9.14, B_DE11.14, B_DE12.14, B_DE13.14, B_E4.16, B_E7.11, B_E14.14, B_E15.14, B_F4.16, B_F13.20, B_F14.20, B_G1.16, B_G2.16, B_G4.16, B_G8.24, B_G9.20, B_G10.16, B_G13.20, B_G14.20, B_H6.1, B_H6.27, B_H6.28, B_H7.1, B_H7.27, B_H7.28, B_H8.1, B_H8.27, B_H8.28, B_H9.1, B_H9.27, B_H9.28, B_H11.1, B_H11.27, B_H11.28, B_H12.1, B_H12.27, B_H12.28, C1.14, C3.1, C3.20, C5.28, C6.16, C7.14, C8.1, C8.27, C8.28, C10.1, C10.27, C10.28, C11.1, C11.4, C11.10, C11.13, C11.14, C12.14, C13.14, C14.1, C14.4, C14.10, C14.13, C14.14, C15.1, C15.7, C15.9, C15.10, C16.4, C16.10, C16.11, C16.13, C16.14, C17.20, CD18.14, D1.1, D1.27, D1.28, D3.1, D3.27, D3.28, D4.10, D4.14, D7.14, D8.1, D8.20, D9.14, D10.1, D10.20, D11.1, D11.20, D16.14, D17.14, DE6.1, DE6.27, DE6.28, DE18.14, DE19.14, E1.1, E1.27, E1.28, E3.1, E3.27, E3.28, E4.14, E5.1, E5.20, E6.1, E6.16, E7.16, E8.16, E10.20, E11.1, E11.16, E12.20, E14.18, E15.18, E17.20, F2.9, F2.14, F3.14, F4.7, F4.9, F4.10, F5.16, F6.1, F6.10, F6.14, F7.11, F7.14, F8.24, F10.24, F14.18, F15.18, F17.20, FG12.29, G2.9, G2.14, G3.14, G4.20, G5.14, G6.1, G6.4, G6.10, G6.13, G6.14, G7.1, G7.10, G7.13, G7.14

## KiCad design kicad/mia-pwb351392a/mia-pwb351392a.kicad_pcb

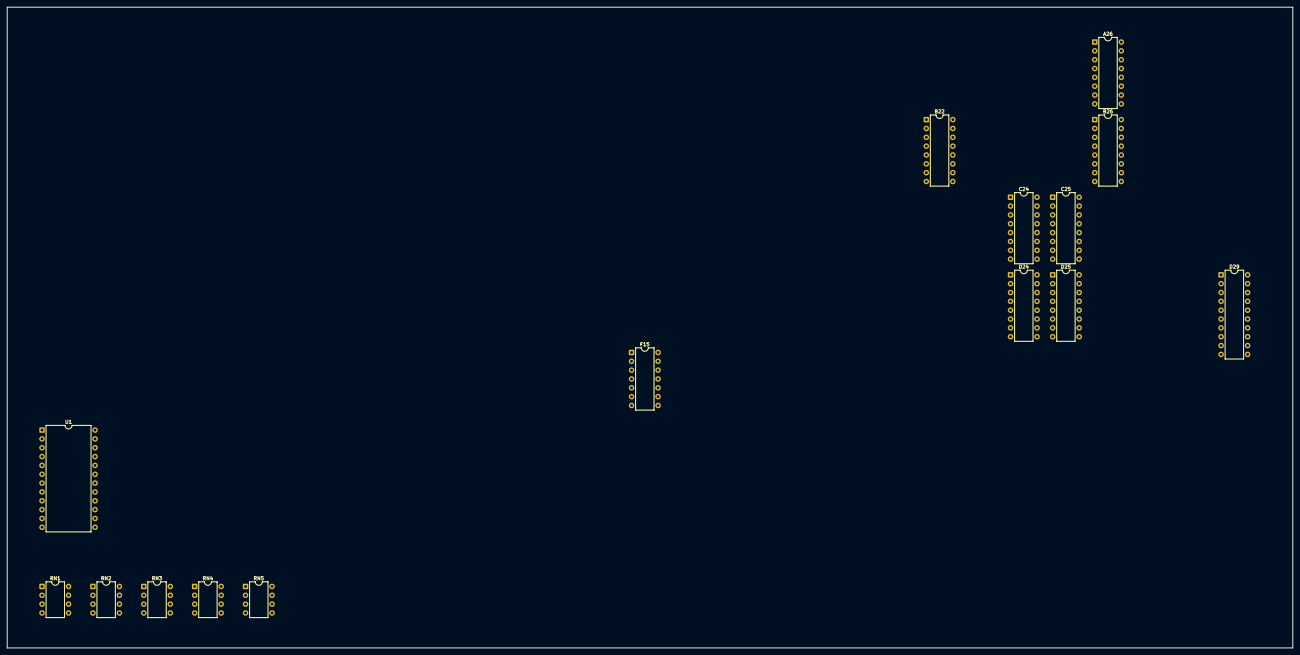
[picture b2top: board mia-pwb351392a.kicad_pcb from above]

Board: 2 copper layers, 369.4 x 184.1 mm, 15 parts (0 on the bottom side), 47 nets, no tracks yet.

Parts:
A26: 74LS257; DIP-16_W7.62mm
B22: 74LS174; DIP-16_W7.62mm
B26: 74LS257; DIP-16_W7.62mm
C24, C25: 74LS253; DIP-16_W7.62mm
D24, D25: 74LS253; DIP-16_W7.62mm
D29: 74LS244; DIP-20_W7.62mm
F15: 74LS04; DIP-14_W7.62mm
RN1, RN2, RN3, RN4, RN5: KONAMI_005273; DIP-8_W7.62mm
U1: 051550; DIP-24_W15.24mm

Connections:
/AB1: A26.1, B26.1, F15.1
/CNT1: U1.22, U1.23
/CNT2: U1.20, U1.21
/D0: A26.4, B22.3, D24.9, D29.12
/D1: A26.7, B22.4, D24.7, D29.14
/D2: A26.12, C24.9, D29.16
/D3: A26.9, B22.11, C24.7, D29.18
/D4: B26.4, D25.9
/D5: B22.13, B26.7, D25.7
/D6: B26.12, C25.9
/D7: B22.14, B26.9, C25.7
/DIP: A26.15, B26.15
/OUT1: B22.2, U1.15
/OUT2: B22.5, U1.16
/~AB1: C24.14, C25.14, D24.14, D25.14, F15.2
/~AB2: C24.2, C25.2, D24.2, D25.2, F15.4
/~RES: B22.1, D29.13, U1.10
/~SHOOT: C24.1, C24.15, C25.1, C25.15, D24.1, D24.15, D25.1, D25.15
unnamed: A26.2, RN3.2
unnamed: A26.11, RN3.4
unnamed: A26.3, RN4.2
unnamed: A26.10, RN4.4
unnamed: B26.2, RN3.6
unnamed: B26.14, RN3.8
unnamed: B26.3, RN4.6
unnamed: B26.13, RN4.8
unnamed: C24.5, RN4.3
unnamed: C24.4, RN4.5
unnamed: C24.12, RN3.3
unnamed: C24.3, RN4.7
unnamed: C25.10, RN1.1
unnamed: C25.11, RN1.3
unnamed: C25.12, RN1.5
unnamed: D24.5, RN3.5
unnamed: D24.11, RN5.3
unnamed: D24.4, RN3.7
unnamed: D24.12, RN5.5
unnamed: D24.3, RN5.1
unnamed: D24.13, RN5.7
unnamed: D25.5, RN1.7
unnamed: D25.12, RN2.7
unnamed: D29.2, RN2.5
unnamed: D29.4, RN2.4
unnamed: D29.6, RN2.3
unnamed: D29.8, RN2.2
VCC: C24.6, C24.10, C24.13, C24.16, C25.3, C25.4, C25.5, C25.6, C25.13, C25.16, D24.6, D24.10, D24.16, D25.3, D25.6, D25.10, D25.16, D29.20, RN2.1, RN3.1, RN4.1
VSS: C24.8, C25.8, D24.8, D25.8, D29.10, D29.19, U1.13, U1.14
